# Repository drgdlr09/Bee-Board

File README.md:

# Bee Board - A Brief Overview

For Half Life week 3, I designed Bee Board, a MIDI controller with 7 hexagon-shaped capacitive touch keys, two sliders, two switches, and two RGB LEDs. I wanted to make a MIDI keyboard that had some sort of theme, and after brainstorming, I decided to lay out my touch buttons like a honeycomb with C in the middle, and G, E, A, F, D, and B around it. Another cool thing about the Bee Board is that you can play chords by placing your finger at the intersection of touch buttons. Since it's a honeycomb, I made a simple bee image and put it on the board as well.

# How It Works

Bee Board has an esp32-s3-zero microcontroller, 7 capacitive touchpads, two slides, two Kailh Choc switches, and two SK6812MINI-E RGB LEDs under the switches. The MIDI is build around the ESP32-S3-Zero. I wanted to add a good amount of features, so this was the right pick for this project. 
The touch pads are hexagons about 24mm across, with 1.2mm gaps between them so touching one pad doesn’t trigger the one next to it. They’re covered by solder mask, so the note letters are printed right on top of them. Touch pad 1 (C) is on GP1, and pads 2 through 7 (G, E, A, F, D, B) are on GP2 through GP7. When a pad is touched, the firmware sends a MIDI Note On message, and when it’s released, it sends Note Off. 
The sliders control how the notes sound. Slider 1 is on GP10 and sets the velocity, which is how loud each note plays. Touch pads can’t tell how hard you press them, so this was the easiest way to change the volume. Slider 2 is on GP11 and sends MIDI CC 1, the modulation wheel, which adds vibrato in most synths.
The switches change the octave. Switch 1 is on RX and moves down an octave, and switch 2 is on TX and moves up an octave. Pressing both resets it to the middle octave. Each switch has an SK6812MINI-E LED mounted under it on the back of the board, shining up through a cutout. The LED data line is on GP12. The first LED changes color to show the octave, and the second lights up blue for a single note and gold for a chord.

## Bill of Materials

| Part | Qty | Unit Price | Total | Vendor |
|------|-----|-----------|-------|--------|
| Waveshare ESP32-S3-Zero | 1 | $5.69 | $5.69 | AliExpress |
| Kailh Choc V2 Low Profile Switches | 5 | $0.63 | $3.15 | AliExpress |
| Bourns PTA1543 Slide Potentiometers (10k) | 2 | $1.58 | $3.16 | DigiKey |
|PCB|1|$9.60|$9.60|JLCPCB|

Tax & shipping: $7.29
**Total**: **$19.29**

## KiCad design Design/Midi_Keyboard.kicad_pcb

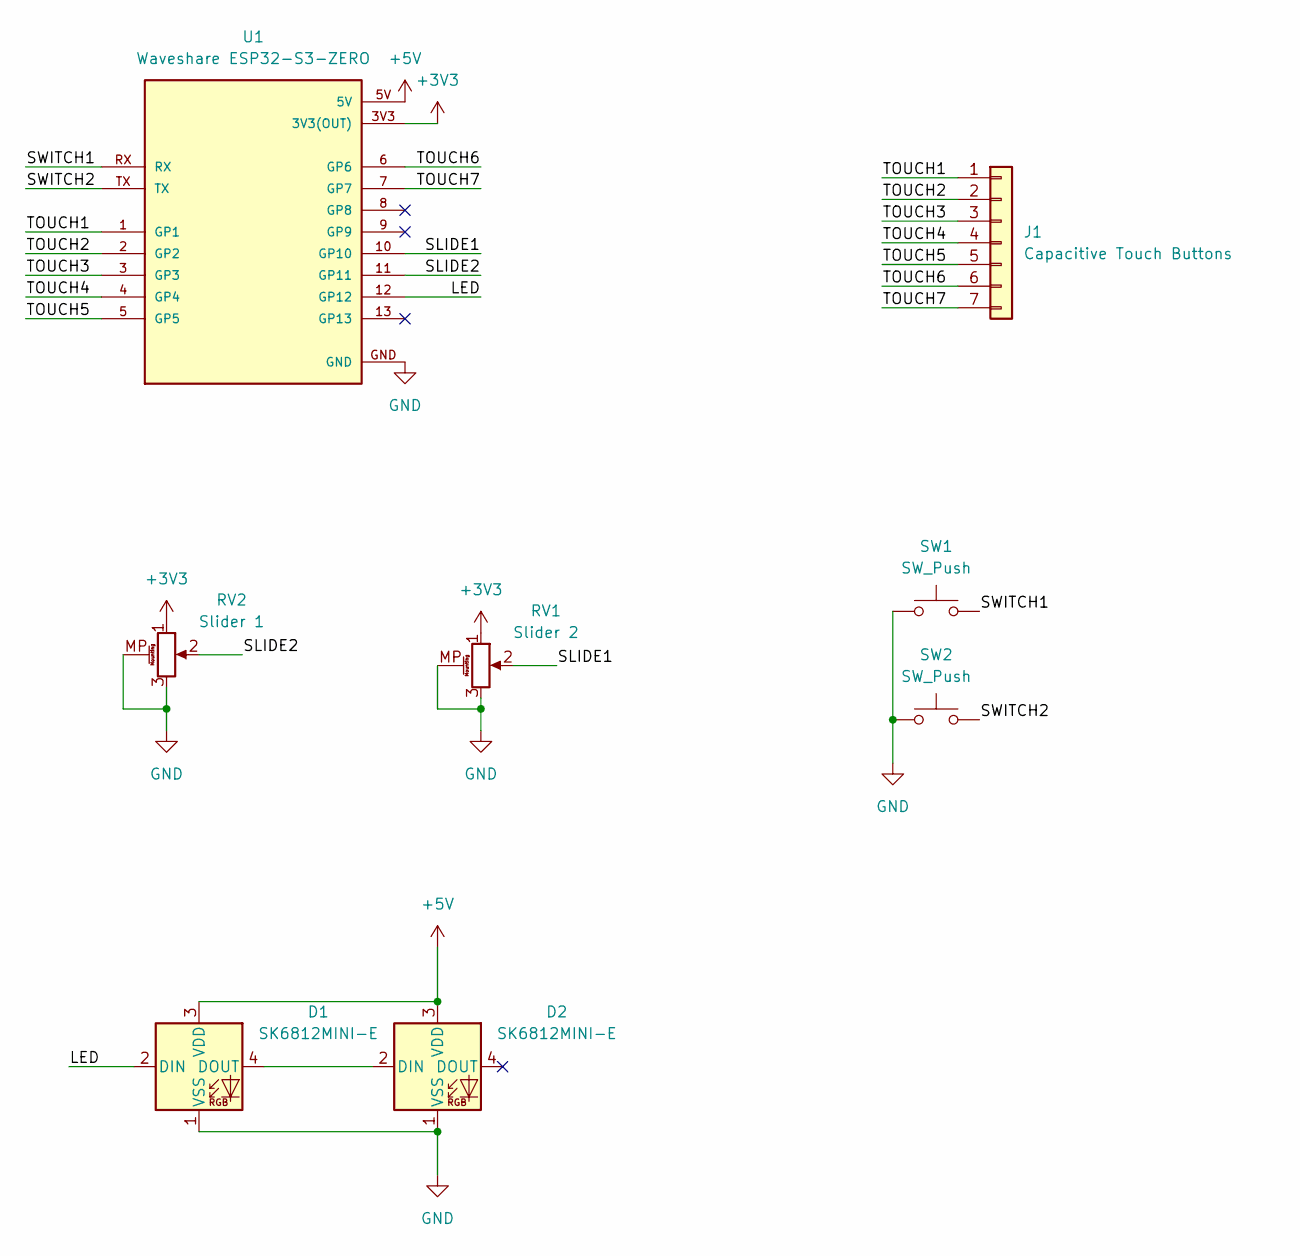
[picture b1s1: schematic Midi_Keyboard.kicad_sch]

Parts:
D1, D2: SK6812MINI-E; LED_SK6812MINI-E_3.2x2.8mm_P1.5mm_ReverseMount
J1: Capacitive Touch Buttons; Touch_Honeycomb_7
RV1: Slider 2; Potentiometer_Bourns_PTA1543_Single_Slide
RV2: Slider 1; Potentiometer_Bourns_PTA1543_Single_Slide
SW1, SW2: SW_Push; Kailh Choc Low-Profile Switches
U1: Waveshare ESP32-S3-ZERO; Waveshare ESP32-S3-Zero; PARTREV NA

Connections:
+3V3: RV1.1, RV2.1, U1.3V3 (3V3(OUT))
+5V: D1.3 (VDD), D2.3 (VDD), U1.5V
GND: D1.1 (VSS), D2.1 (VSS), RV1.3, RV1.MP (MountPin), RV2.3, RV2.MP (MountPin), SW1.1, SW2.1, U1.GND
LED: D1.2 (DIN), U1.12 (GP12)
N$D1.4_D2.2: D1.4 (DOUT), D2.2 (DIN)
SLIDE1: RV1.2, U1.10 (GP10)
SLIDE2: RV2.2, U1.11 (GP11)
SWITCH1: SW1.2, U1.RX
SWITCH2: SW2.2, U1.TX
TOUCH1: J1.1, U1.1 (GP1)
TOUCH2: J1.2, U1.2 (GP2)
TOUCH3: J1.3, U1.3 (GP3)
TOUCH4: J1.4, U1.4 (GP4)
TOUCH5: J1.5, U1.5 (GP5)
TOUCH6: J1.6, U1.6 (GP6)
TOUCH7: J1.7, U1.7 (GP7)

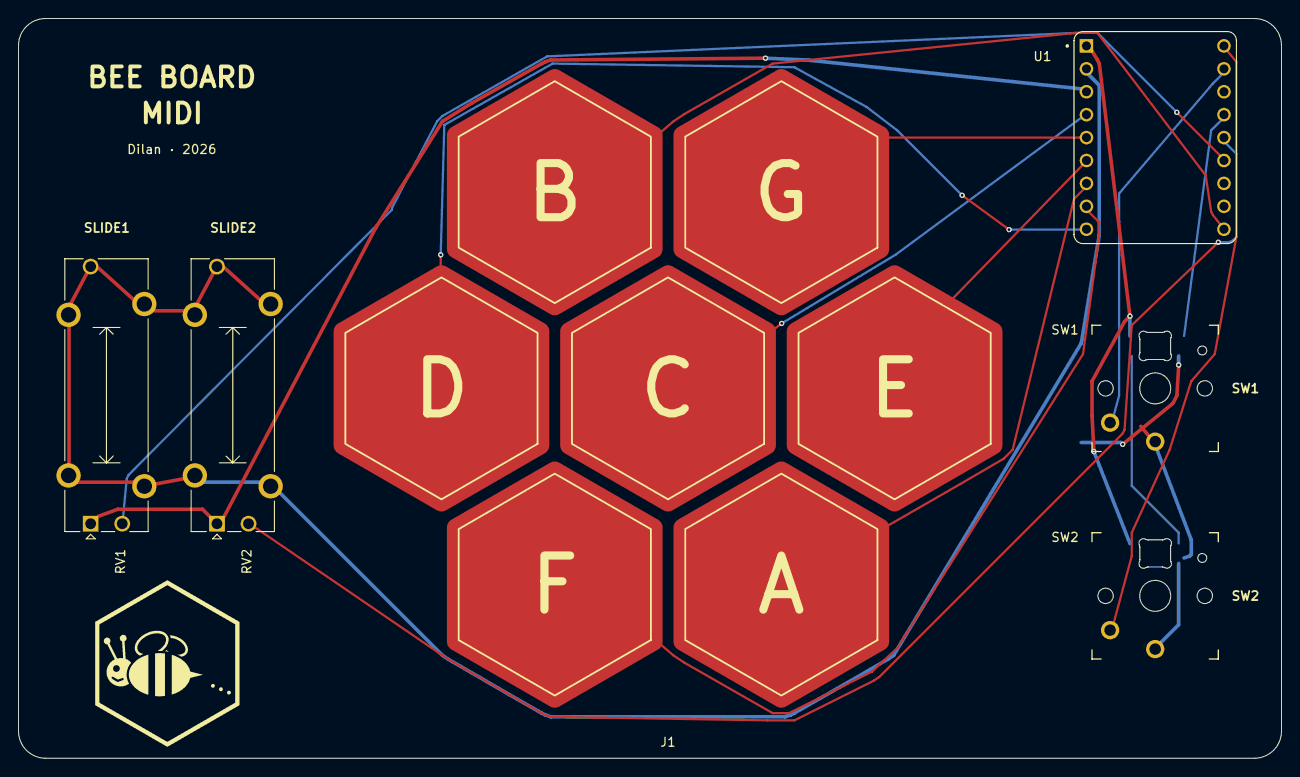
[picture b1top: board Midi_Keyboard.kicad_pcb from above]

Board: 2 copper layers, 140.0 x 82.0 mm, 9 parts (0 on the bottom side), 16 nets.

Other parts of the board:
G1: Bee_Logo

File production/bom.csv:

Designator,Footprint,Quantity,Value,LCSC Part #
"D1, D2",LED_SK6812MINI-E_3.2x2.8mm_P1.5mm_ReverseMount,2,SK6812MINI-E,
J1,Touch_Honeycomb_7,1,Capacitive Touch Buttons,
RV1,Potentiometer_Bourns_PTA1543_Single_Slide,1,Slider 2,
RV2,Potentiometer_Bourns_PTA1543_Single_Slide,1,Slider 1,
"SW1, SW2",Kailh Choc Low-Profile Switches,2,SW_Push,
U1,Waveshare ESP32-S3-Zero,1,Waveshare ESP32-S3-ZERO,
